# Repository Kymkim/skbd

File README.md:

# SKBD

!WORK IN PROGRESS

This is a keyboard project that I have been working on. This unlike your normal keyboard. This keyboard aims to solve my headaches with traditioal keyboards

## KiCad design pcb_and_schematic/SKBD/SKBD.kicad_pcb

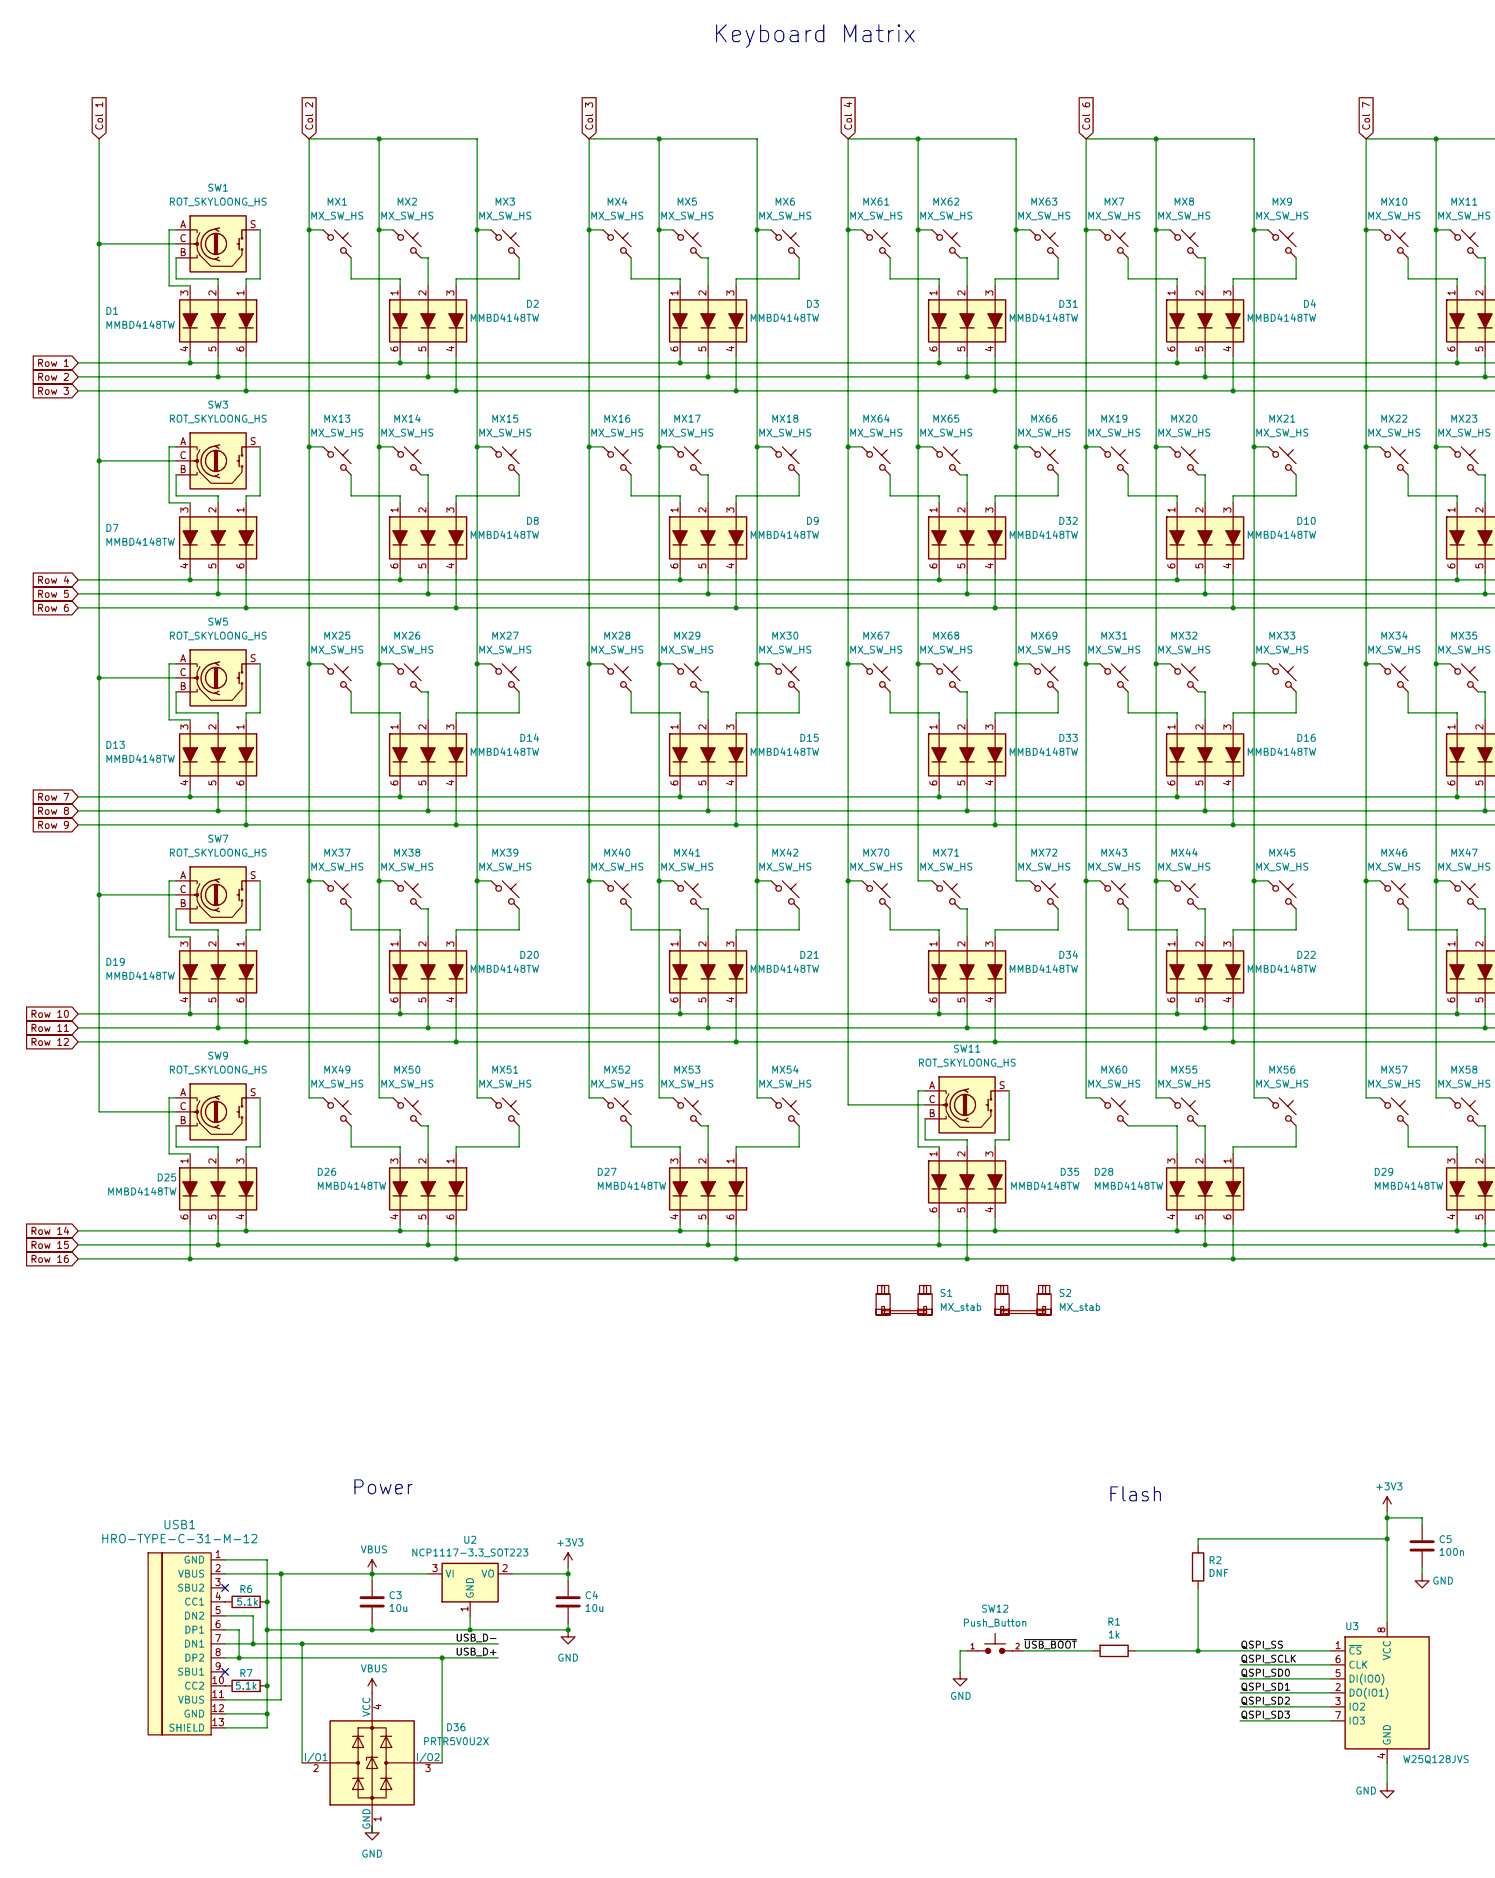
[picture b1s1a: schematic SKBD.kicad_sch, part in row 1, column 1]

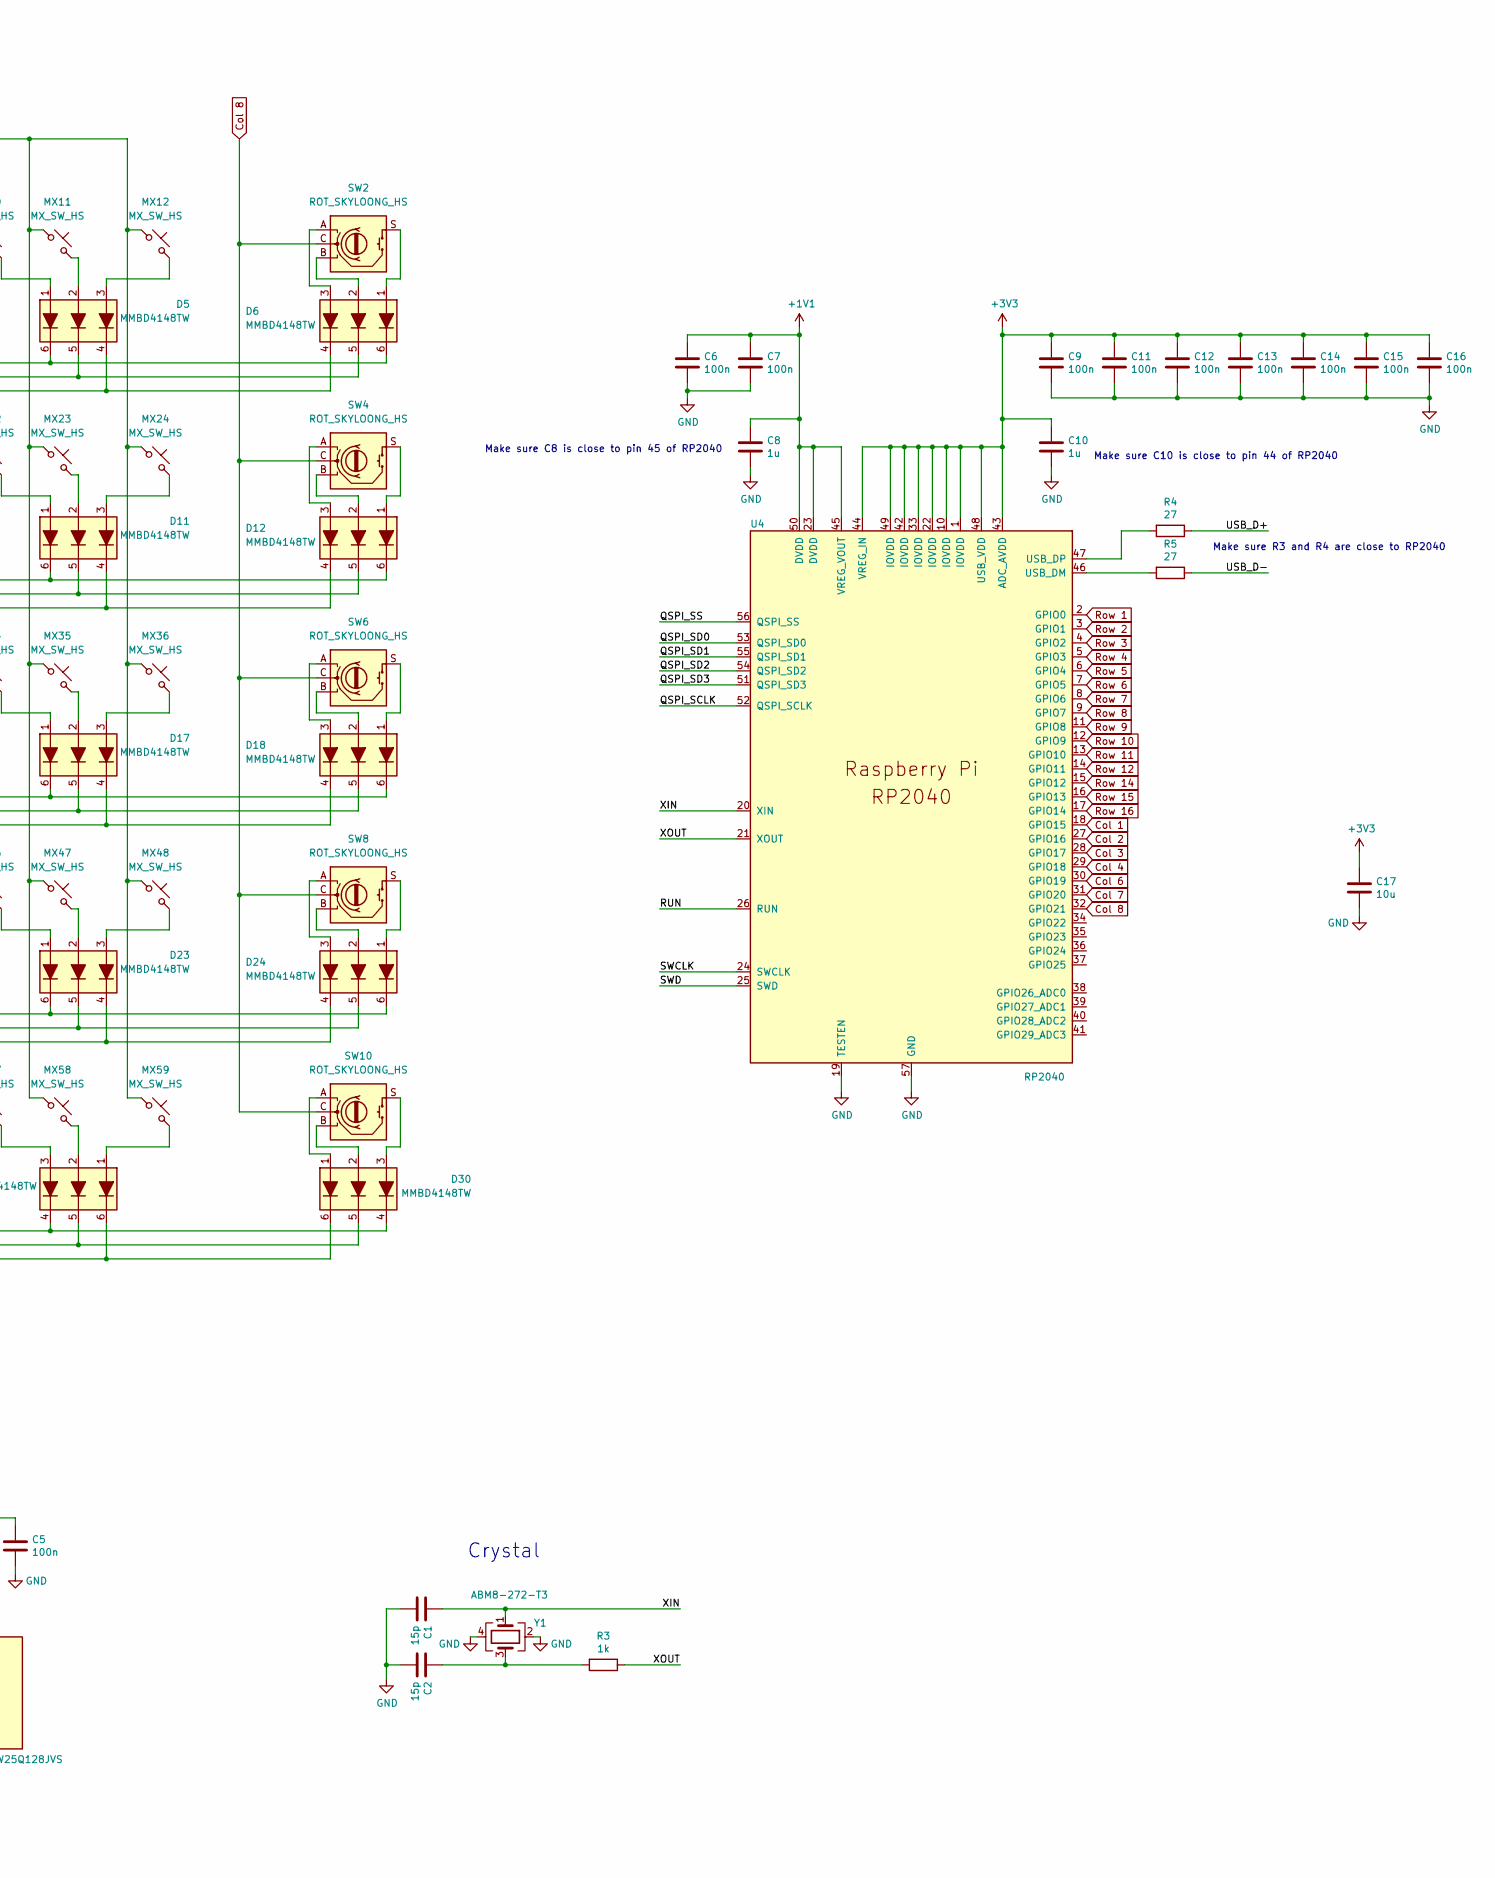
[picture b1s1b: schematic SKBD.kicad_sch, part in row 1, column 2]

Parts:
C1, C2: 15p; C_0402_1005Metric
C3, C4, C17: 10u; C_0402_1005Metric
C5, C6, C7, C9, C11, C12, C13, C14, C15, C16: 100n; C_0402_1005Metric
C8, C10: 1u; C_0402_1005Metric
D1, D2, D3, D4, D5, D6, D7, D8, D9, D10, D11, D12, D13, D14, D15, D16, D17, D18, D19, D20, D21, D22, D23, D24, D25, D26, D27, D28, D29, D30, D31, D32, D33, D34, D35: MMBD4148TW; SOT-363_SC-70-6
D36: PRTR5V0U2X; SOT-143
MX1, MX2, MX3, MX4, MX5, MX6, MX7, MX8, MX9, MX10, MX11, MX12, MX13, MX14, MX15, MX16, MX17, MX18, MX19, MX20, MX21, MX22, MX23, MX24, MX25, MX26, MX27, MX28, MX29, MX30, MX31, MX32, MX33, MX34, MX35, MX36, MX37, MX38, MX39, MX40, MX41, MX42, MX43, MX44, MX45, MX46, MX47, MX48, MX49, MX50, MX51, MX52, MX53, MX54, MX55, MX56, MX57, MX58, MX59, MX60, MX61, MX62, MX63, MX64, MX65, MX66, MX67, MX68, MX69, MX70, MX71, MX72: MX_SW_HS; SW_MX_HS_CPG151101S11_1u
R1, R3: 1k; R_0402_1005Metric
R2: DNF; R_0402_1005Metric
R4, R5: 27; R_0402_1005Metric
R6, R7: 5.1k; R_0402_1005Metric
S1, S2: MX_stab; STAB_MX_P_2u
SW1, SW2, SW3, SW4, SW5, SW6, SW7, SW8, SW9, SW10, SW11: ROT_SKYLOONG_HS; ROT_SKYLOONG_HS-Switch
SW12: Push_Button; SW_SPST_SKQG_WithStem
U2: NCP1117-3.3_SOT223; SOT-223-3_TabPin2
U3: W25Q128JVS; SOIC-8_5.23x5.23mm_P1.27mm
U4: RP2040; QFN-56-1EP_7x7mm_P0.4mm_EP3.2x3.2mm
USB1: HRO-TYPE-C-31-M-12; HRO-TYPE-C-31-M-12-Assembly
Y1: ABM8-272-T3; Crystal_SMD_3225-4Pin_3.2x2.5mm

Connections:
+1V1: C6.1, C7.1, C8.1, U4.23 (DVDD), U4.45 (VREG_VOUT), U4.50 (DVDD)
+3V3: C4.1, C5.1, C9.1, C10.1, C11.1, C12.1, C13.1, C14.1, C15.1, C16.1, C17.1, R2.1, U2.2 (VO), U3.8 (VCC), U4.1 (IOVDD), U4.10 (IOVDD), U4.22 (IOVDD), U4.33 (IOVDD), U4.42 (IOVDD), U4.43 (ADC_AVDD), U4.44 (VREG_IN), U4.48 (USB_VDD), U4.49 (IOVDD)
/QSPI_SCLK: U3.6 (CLK), U4.52 (QSPI_SCLK)
/QSPI_SD0: U3.5 (DI(IO0)), U4.53 (QSPI_SD0)
/QSPI_SD1: U3.2 (DO(IO1)), U4.55 (QSPI_SD1)
/QSPI_SD2: U3.3 (IO2), U4.54 (QSPI_SD2)
/QSPI_SD3: U3.7 (IO3), U4.51 (QSPI_SD3)
/QSPI_SS: R1.1, R2.2, U3.1 (~CS), U4.56 (QSPI_SS)
/RUN: U4.26 (RUN)
/SWCLK: U4.24 (SWCLK)
/SWD: U4.25 (SWD)
/USB_D+: D36.3 (I/O2), R4.1, USB1.6 (DP1), USB1.8 (DP2)
/USB_D-: D36.2 (I/O1), R5.1, USB1.5 (DN2), USB1.7 (DN1)
/XIN: C1.1, U4.20 (XIN), Y1.1
/XOUT: R3.1, U4.21 (XOUT)
/~USB_BOOT: R1.2, SW12.2
Col 1: SW1.C, SW3.C, SW5.C, SW7.C, SW9.C, U4.18 (GPIO15)
Col 2: MX1.1, MX2.1, MX3.1, MX13.1, MX14.1, MX15.1, MX25.1, MX26.1, MX27.1, MX37.1, MX38.1, MX39.1, MX49.1, MX50.1, MX51.1, U4.27 (GPIO16)
Col 3: MX4.1, MX5.1, MX6.1, MX16.1, MX17.1, MX18.1, MX28.1, MX29.1, MX30.1, MX40.1, MX41.1, MX42.1, MX52.1, MX53.1, MX54.1, U4.28 (GPIO17)
Col 4: MX61.1, MX62.1, MX63.1, MX64.1, MX65.1, MX66.1, MX67.1, MX68.1, MX69.1, MX70.1, MX71.1, MX72.1, SW11.C, U4.29 (GPIO18)
Col 6: MX7.1, MX8.1, MX9.1, MX19.1, MX20.1, MX21.1, MX31.1, MX32.1, MX33.1, MX43.1, MX44.1, MX45.1, MX55.1, MX56.1, MX60.1, U4.30 (GPIO19)
Col 7: MX10.1, MX11.1, MX12.1, MX22.1, MX23.1, MX24.1, MX34.1, MX35.1, MX36.1, MX46.1, MX47.1, MX48.1, MX57.1, MX58.1, MX59.1, U4.31 (GPIO20)
Col 8: SW2.C, SW4.C, SW6.C, SW8.C, SW10.C, U4.32 (GPIO21)
GND: C1.2, C2.2, C3.2, C4.2, C5.2, C6.2, C7.2, C8.2, C9.2, C10.2, C11.2, C12.2, C13.2, C14.2, C15.2, C16.2, C17.2, D36.1 (GND), R6.2, R7.2, SW12.1, U2.1 (GND), U3.4 (GND), U4.19 (TESTEN), U4.57 (GND), USB1.1 (GND), USB1.12 (GND), USB1.13 (SHIELD), Y1.2, Y1.4
unnamed: C2.1, R3.2, Y1.3
unnamed: D1.1 (A1), SW1.S
unnamed: D1.2 (A2), SW1.B
unnamed: D1.3 (A3), SW1.A
unnamed: D2.1 (A1), MX1.2
unnamed: D2.2 (A2), MX2.2
unnamed: D2.3 (A3), MX3.2
unnamed: D3.1 (A1), MX4.2
unnamed: D3.2 (A2), MX5.2
unnamed: D3.3 (A3), MX6.2
unnamed: D4.1 (A1), MX7.2
unnamed: D4.2 (A2), MX8.2
unnamed: D4.3 (A3), MX9.2
unnamed: D5.1 (A1), MX10.2
unnamed: D5.2 (A2), MX11.2
unnamed: D5.3 (A3), MX12.2
unnamed: D6.1 (A1), SW2.S
unnamed: D6.2 (A2), SW2.B
unnamed: D6.3 (A3), SW2.A
unnamed: D7.1 (A1), SW3.S
unnamed: D7.2 (A2), SW3.B
unnamed: D7.3 (A3), SW3.A
unnamed: D8.1 (A1), MX13.2
unnamed: D8.2 (A2), MX14.2
unnamed: D8.3 (A3), MX15.2
unnamed: D9.1 (A1), MX16.2
unnamed: D9.2 (A2), MX17.2
unnamed: D9.3 (A3), MX18.2
unnamed: D10.1 (A1), MX19.2
unnamed: D10.2 (A2), MX20.2
unnamed: D10.3 (A3), MX21.2
unnamed: D11.1 (A1), MX22.2
unnamed: D11.2 (A2), MX23.2
unnamed: D11.3 (A3), MX24.2
unnamed: D12.1 (A1), SW4.S
unnamed: D12.2 (A2), SW4.B
unnamed: D12.3 (A3), SW4.A
unnamed: D13.1 (A1), SW5.S
unnamed: D13.2 (A2), SW5.B
unnamed: D13.3 (A3), SW5.A
unnamed: D14.1 (A1), MX25.2
unnamed: D14.2 (A2), MX26.2
unnamed: D14.3 (A3), MX27.2
unnamed: D15.1 (A1), MX28.2
unnamed: D15.2 (A2), MX29.2
unnamed: D15.3 (A3), MX30.2
unnamed: D16.1 (A1), MX31.2
unnamed: D16.2 (A2), MX32.2
unnamed: D16.3 (A3), MX33.2
unnamed: D17.1 (A1), MX34.2
unnamed: D17.2 (A2), MX35.2
unnamed: D17.3 (A3), MX36.2
unnamed: D18.1 (A1), SW6.S
unnamed: D18.2 (A2), SW6.B
unnamed: D18.3 (A3), SW6.A
unnamed: D19.1 (A1), SW7.S
unnamed: D19.2 (A2), SW7.B
unnamed: D19.3 (A3), SW7.A
unnamed: D20.1 (A1), MX37.2
unnamed: D20.2 (A2), MX38.2
unnamed: D20.3 (A3), MX39.2
unnamed: D21.1 (A1), MX40.2
unnamed: D21.2 (A2), MX41.2
unnamed: D21.3 (A3), MX42.2
unnamed: D22.1 (A1), MX43.2
unnamed: D22.2 (A2), MX44.2
unnamed: D22.3 (A3), MX45.2
unnamed: D23.1 (A1), MX46.2
unnamed: D23.2 (A2), MX47.2
unnamed: D23.3 (A3), MX48.2
unnamed: D24.1 (A1), SW8.S
unnamed: D24.2 (A2), SW8.B
unnamed: D24.3 (A3), SW8.A
unnamed: D25.1 (A1), SW9.A
unnamed: D25.2 (A2), SW9.B
unnamed: D25.3 (A3), SW9.S
unnamed: D26.1 (A1), MX51.2
unnamed: D26.2 (A2), MX50.2
unnamed: D26.3 (A3), MX49.2
unnamed: D27.1 (A1), MX54.2
unnamed: D27.2 (A2), MX53.2
unnamed: D27.3 (A3), MX52.2
unnamed: D28.1 (A1), MX56.2
unnamed: D28.2 (A2), MX55.2
unnamed: D28.3 (A3), MX60.2
unnamed: D29.1 (A1), MX59.2
unnamed: D29.2 (A2), MX58.2
unnamed: D29.3 (A3), MX57.2
unnamed: D30.1 (A1), SW10.A
unnamed: D30.2 (A2), SW10.B
unnamed: D30.3 (A3), SW10.S
unnamed: D31.1 (A1), MX61.2
unnamed: D31.2 (A2), MX62.2
unnamed: D31.3 (A3), MX63.2
unnamed: D32.1 (A1), MX64.2
unnamed: D32.2 (A2), MX65.2
unnamed: D32.3 (A3), MX66.2
unnamed: D33.1 (A1), MX67.2
unnamed: D33.2 (A2), MX68.2
unnamed: D33.3 (A3), MX69.2
unnamed: D34.1 (A1), MX70.2
unnamed: D34.2 (A2), MX71.2
unnamed: D34.3 (A3), MX72.2
unnamed: D35.1 (A1), SW11.A
unnamed: D35.2 (A2), SW11.B
unnamed: D35.3 (A3), SW11.S
unnamed: R5.2, U4.46 (USB_DM)
unnamed: R4.2, U4.47 (USB_DP)
unnamed: R6.1, USB1.4 (CC1)
unnamed: R7.1, USB1.10 (CC2)
Row 1: D1.4 (K3), D2.6 (K1), D3.6 (K1), D4.6 (K1), D5.6 (K1), D6.6 (K1), D31.6 (K1), U4.2 (GPIO0)
Row 2: D1.5 (K2), D2.5 (K2), D3.5 (K2), D4.5 (K2), D5.5 (K2), D6.5 (K2), D31.5 (K2), U4.3 (GPIO1)
Row 3: D1.6 (K1), D2.4 (K3), D3.4 (K3), D4.4 (K3), D5.4 (K3), D6.4 (K3), D31.4 (K3), U4.4 (GPIO2)
Row 4: D7.4 (K3), D8.6 (K1), D9.6 (K1), D10.6 (K1), D11.6 (K1), D12.6 (K1), D32.6 (K1), U4.5 (GPIO3)
Row 5: D7.5 (K2), D8.5 (K2), D9.5 (K2), D10.5 (K2), D11.5 (K2), D12.5 (K2), D32.5 (K2), U4.6 (GPIO4)
Row 6: D7.6 (K1), D8.4 (K3), D9.4 (K3), D10.4 (K3), D11.4 (K3), D12.4 (K3), D32.4 (K3), U4.7 (GPIO5)
Row 7: D13.4 (K3), D14.6 (K1), D15.6 (K1), D16.6 (K1), D17.6 (K1), D18.6 (K1), D33.6 (K1), U4.8 (GPIO6)
Row 8: D13.5 (K2), D14.5 (K2), D15.5 (K2), D16.5 (K2), D17.5 (K2), D18.5 (K2), D33.5 (K2), U4.9 (GPIO7)
Row 9: D13.6 (K1), D14.4 (K3), D15.4 (K3), D16.4 (K3), D17.4 (K3), D18.4 (K3), D33.4 (K3), U4.11 (GPIO8)
Row 10: D19.4 (K3), D20.6 (K1), D21.6 (K1), D22.6 (K1), D23.6 (K1), D24.6 (K1), D34.6 (K1), U4.12 (GPIO9)
Row 11: D19.5 (K2), D20.5 (K2), D21.5 (K2), D22.5 (K2), D23.5 (K2), D24.5 (K2), D34.5 (K2), U4.13 (GPIO10)
Row 12: D19.6 (K1), D20.4 (K3), D21.4 (K3), D22.4 (K3), D23.4 (K3), D24.4 (K3), D34.4 (K3), U4.14 (GPIO11)
Row 14: D25.4 (K3), D26.4 (K3), D27.4 (K3), D28.4 (K3), D29.4 (K3), D30.4 (K3), D35.4 (K3), U4.15 (GPIO12)
Row 15: D25.5 (K2), D26.5 (K2), D27.5 (K2), D28.5 (K2), D29.5 (K2), D30.5 (K2), D35.6 (K1), U4.16 (GPIO13)
Row 16: D25.6 (K1), D26.6 (K1), D27.6 (K1), D28.6 (K1), D29.6 (K1), D30.6 (K1), D35.5 (K2), U4.17 (GPIO14)
VBUS: C3.1, D36.4 (VCC), U2.3 (VI), USB1.2 (VBUS), USB1.11 (VBUS)

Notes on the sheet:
Make sure C8 is close to pin 45 of RP2040
Power
Crystal
Make sure C10 is close to pin 44 of RP2040
Keyboard Matrix
Flash
Make sure R3 and R4 are close to RP2040

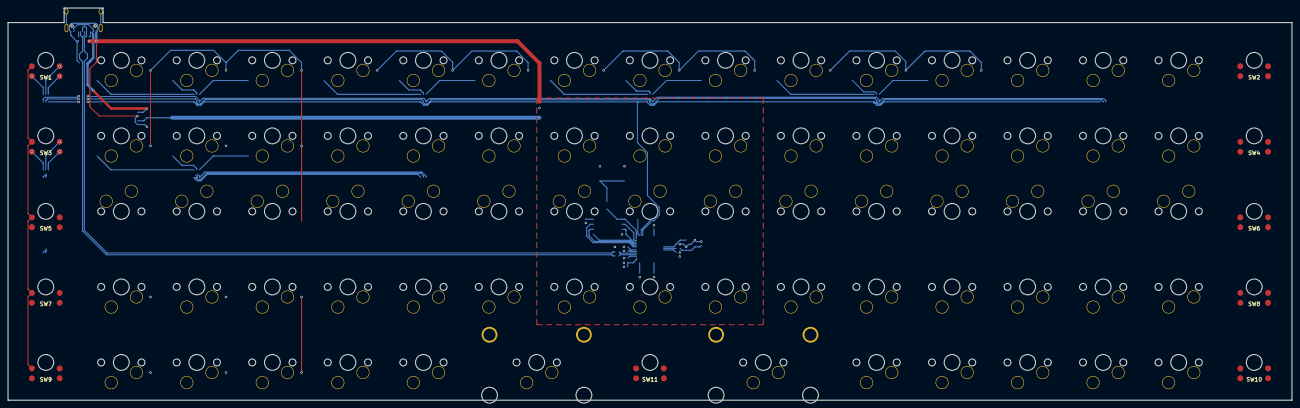
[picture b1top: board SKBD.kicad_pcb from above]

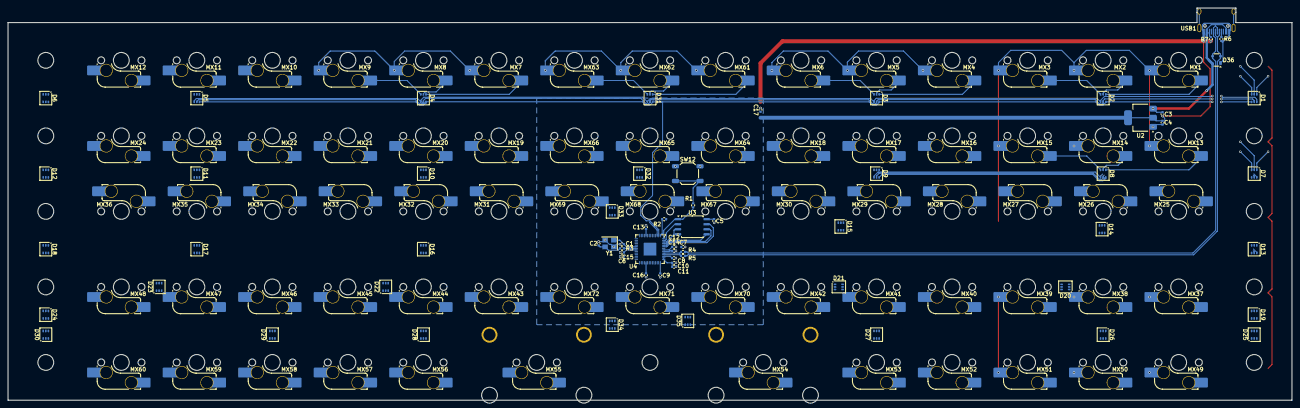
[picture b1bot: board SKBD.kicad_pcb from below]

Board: 2 copper layers, 323.9 x 98.9 mm, 151 parts (138 on the bottom side), 147 nets.

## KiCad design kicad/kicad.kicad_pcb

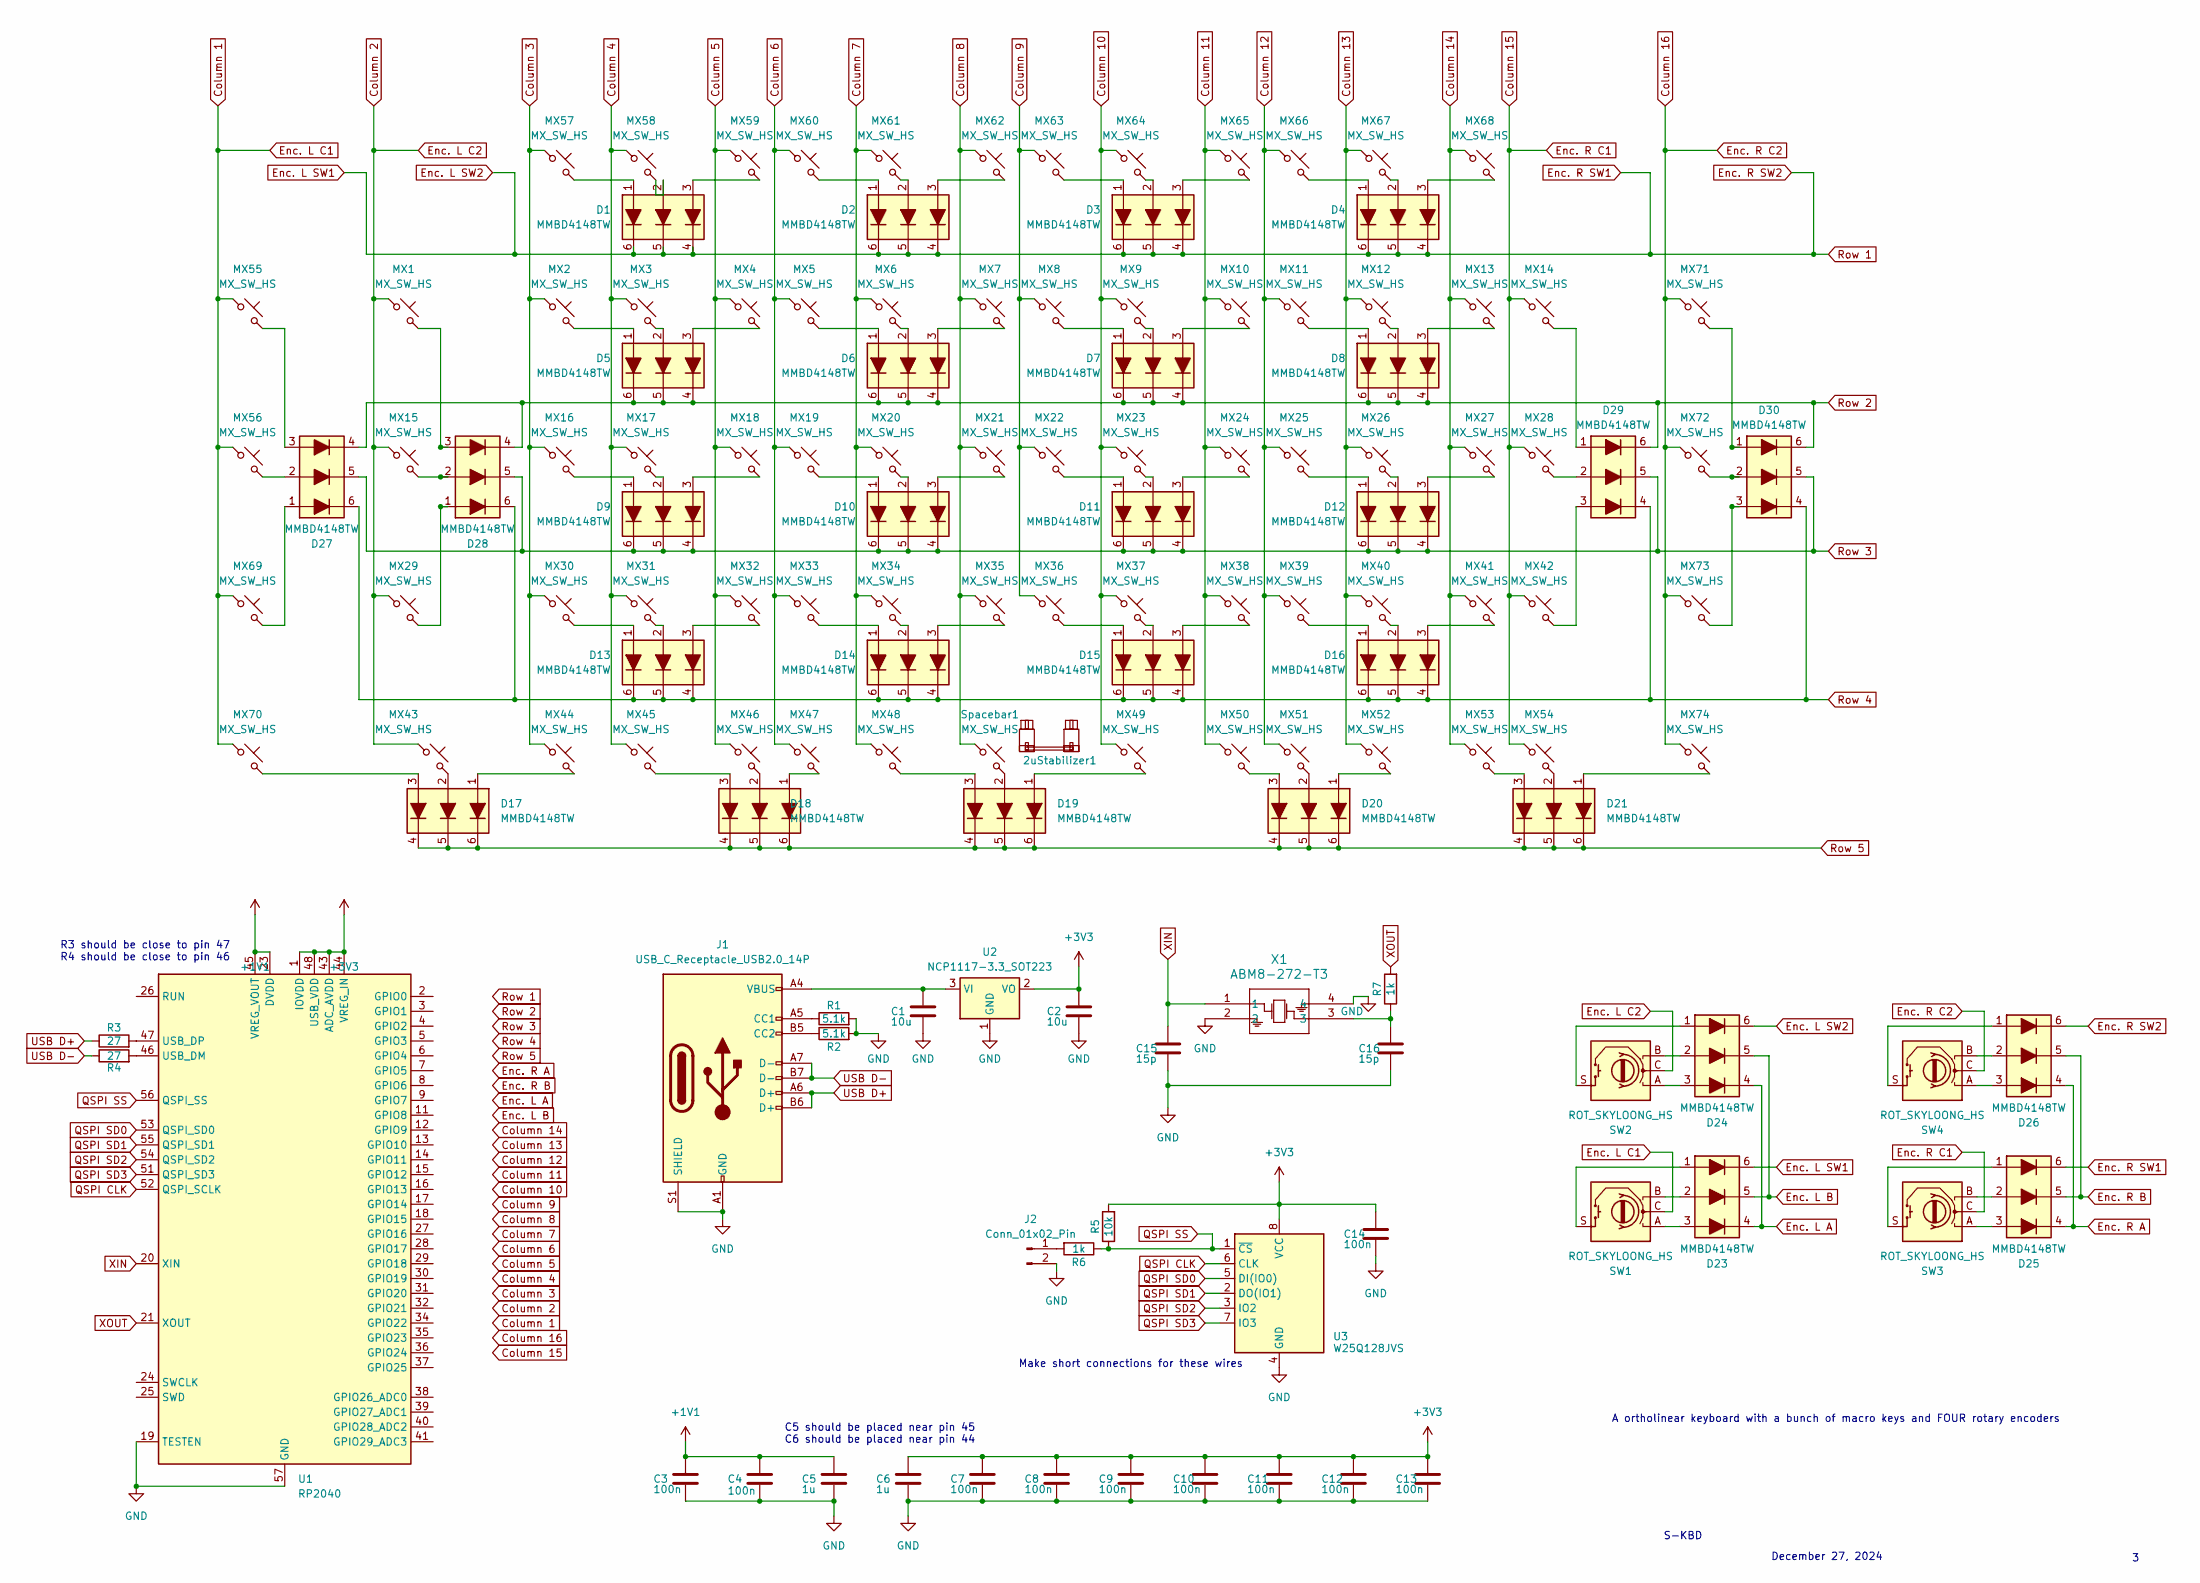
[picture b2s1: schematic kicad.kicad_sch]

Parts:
2uStabilizer1: MX_stab; STAB_MX_2u
C1, C2: 10u; C_01005_0402Metric
C3, C4, C7, C8, C9, C10, C11, C12, C13, C14: 100n; C_01005_0402Metric
C5, C6: 1u; C_01005_0402Metric
C15, C16: 15p; C_01005_0402Metric
D1, D2, D3, D4, D5, D6, D7, D8, D9, D10, D11, D12, D13, D14, D15, D16, D17, D18, D19, D20, D21, D23, D24, D25, D26, D27, D28, D29, D30: MMBD4148TW; SOT-363_SC-70-6
J1: USB_C_Receptacle_USB2.0_14P; USB_C_Receptacle_JAE_DX07S016JA1R1500
J2: Conn_01x02_Pin; PinHeader_1x02_P1.00mm_Horizontal
MX1, MX2, MX3, MX4, MX5, MX6, MX7, MX8, MX9, MX10, MX11, MX12, MX13, MX14, MX15, MX16, MX17, MX18, MX19, MX20, MX21, MX22, MX23, MX24, MX25, MX26, MX27, MX28, MX29, MX30, MX31, MX32, MX33, MX34, MX35, MX36, MX37, MX38, MX39, MX40, MX41, MX42, MX43, MX44, MX45, MX46, MX47, MX48, MX49, MX50, MX51, MX52, MX53, MX54, MX55, MX56, MX57, MX58, MX59, MX60, MX61, MX62, MX63, MX64, MX65, MX66, MX67, MX68, MX69, MX70, MX71, MX72, MX73, MX74: MX_SW_HS; SW_MX_HS_CPG151101S11_1u
R1, R2: 5.1k; R_01005_0402Metric
R3, R4: 27; R_01005_0402Metric
R5: 10k; R_01005_0402Metric
R6, R7: 1k; R_01005_0402Metric
SW1, SW2, SW3, SW4: ROT_SKYLOONG_HS; ROT_SKYLOONG_HS-Switch
Spacebar1: MX_SW_HS; SW_MX_HS_CPG151101S11_1u
U1: RP2040; QFN-56-1EP_7x7mm_P0.4mm_EP3.2x3.2mm
U2: NCP1117-3.3_SOT223; SOT-223-3_TabPin2
U3: W25Q128JVS; SOIC-8_5.23x5.23mm_P1.27mm
X1: ABM8-272-T3; ABM8-272-T3_ABR

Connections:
+1V1: C3.1, C4.1, C5.1, U1.23 (DVDD), U1.45 (VREG_VOUT), U1.50 (DVDD)
+3V3: C2.1, C6.1, C7.1, C8.1, C9.1, C10.1, C11.1, C12.1, C13.1, C14.1, R5.2, U1.1 (IOVDD), U1.10 (IOVDD), U1.22 (IOVDD), U1.33 (IOVDD), U1.42 (IOVDD), U1.43 (ADC_AVDD), U1.44 (VREG_IN), U1.48 (USB_VDD), U1.49 (IOVDD), U2.2 (VO), U3.8 (VCC)
Column 1: MX55.1, MX56.1, MX69.1, MX70.1, SW1.C
Column 2: MX1.1, MX15.1, MX29.1, MX43.1, SW2.C
Column 3: MX2.1, MX16.1, MX30.1, MX44.1, MX57.1
Column 4: MX3.1, MX17.1, MX31.1, MX45.1, MX58.1
Column 5: MX4.1, MX18.1, MX32.1, MX46.1, MX59.1
Column 6: MX5.1, MX19.1, MX33.1, MX47.1, MX60.1
Column 7: MX6.1, MX20.1, MX34.1, MX48.1, MX61.1
Column 8: MX7.1, MX21.1, MX35.1, MX62.1, Spacebar1.1
Column 9: MX8.1, MX22.1, MX36.1, MX63.1
Column 10: MX9.1, MX23.1, MX37.1, MX49.1, MX64.1
Column 11: MX10.1, MX24.1, MX38.1, MX50.1, MX65.1
Column 12: MX11.1, MX25.1, MX39.1, MX51.1, MX66.1
Column 13: MX12.1, MX26.1, MX40.1, MX52.1, MX67.1
Column 14: MX13.1, MX27.1, MX41.1, MX53.1, MX68.1
Column 15: MX14.1, MX28.1, MX42.1, MX54.1, SW3.C
Column 16: MX71.1, MX72.1, MX73.1, MX74.1, SW4.C
Enc. L A: D23.4 (K3), D24.4 (K3)
Enc. L B: D23.5 (K2), D24.5 (K2)
Enc. L SW1: D1.4 (K3), D1.5 (K2), D1.6 (K1), D2.4 (K3), D2.5 (K2), D2.6 (K1), D3.4 (K3), D3.5 (K2), D3.6 (K1), D4.4 (K3), D4.5 (K2), D4.6 (K1), D23.6 (K1), D24.6 (K1), D25.6 (K1), D26.6 (K1)
Enc. R A: D25.4 (K3), D26.4 (K3)
Enc. R B: D25.5 (K2), D26.5 (K2)
GND: C1.2, C2.2, C3.2, C4.2, C5.2, C6.2, C7.2, C8.2, C9.2, C10.2, C11.2, C12.2, C13.2, C14.2, C15.2, C16.2, J1.A1 (GND), J1.A12 (GND), J1.B1 (GND), J1.B12 (GND), J1.S1 (SHIELD), J2.2, R1.2, R2.2, U1.19 (TESTEN), U1.57 (GND), U2.1 (GND), U3.4 (GND), X1.2, X1.4
unnamed: C16.1, R7.1, X1.3
unnamed: D1.1 (A1), MX57.2
unnamed: D1.2 (A2), MX58.2
unnamed: D1.3 (A3), MX59.2
unnamed: D2.1 (A1), MX60.2
unnamed: D2.2 (A2), MX61.2
unnamed: D2.3 (A3), MX62.2
unnamed: D3.1 (A1), MX63.2
unnamed: D3.2 (A2), MX64.2
unnamed: D3.3 (A3), MX65.2
unnamed: D4.1 (A1), MX66.2
unnamed: D4.2 (A2), MX67.2
unnamed: D4.3 (A3), MX68.2
unnamed: D5.1 (A1), MX2.2
unnamed: D5.2 (A2), MX3.2
unnamed: D5.3 (A3), MX4.2
unnamed: D6.1 (A1), MX5.2
unnamed: D6.2 (A2), MX6.2
unnamed: D6.3 (A3), MX7.2
unnamed: D7.1 (A1), MX8.2
unnamed: D7.2 (A2), MX9.2
unnamed: D7.3 (A3), MX10.2
unnamed: D8.1 (A1), MX11.2
unnamed: D8.2 (A2), MX12.2
unnamed: D8.3 (A3), MX13.2
unnamed: D9.1 (A1), MX16.2
unnamed: D9.2 (A2), MX17.2
unnamed: D9.3 (A3), MX18.2
unnamed: D10.1 (A1), MX19.2
unnamed: D10.2 (A2), MX20.2
unnamed: D10.3 (A3), MX21.2
unnamed: D11.1 (A1), MX22.2
unnamed: D11.2 (A2), MX23.2
unnamed: D11.3 (A3), MX24.2
unnamed: D12.1 (A1), MX25.2
unnamed: D12.2 (A2), MX26.2
unnamed: D12.3 (A3), MX27.2
unnamed: D13.1 (A1), MX30.2
unnamed: D13.2 (A2), MX31.2
unnamed: D13.3 (A3), MX32.2
unnamed: D14.1 (A1), MX33.2
unnamed: D14.2 (A2), MX34.2
unnamed: D14.3 (A3), MX35.2
unnamed: D15.1 (A1), MX36.2
unnamed: D15.2 (A2), MX37.2
unnamed: D15.3 (A3), MX38.2
unnamed: D16.1 (A1), MX39.2
unnamed: D16.2 (A2), MX40.2
unnamed: D16.3 (A3), MX41.2
unnamed: D17.1 (A1), MX44.2
unnamed: D17.2 (A2), MX43.2
unnamed: D17.3 (A3), MX70.2
unnamed: D18.1 (A1), MX47.2
unnamed: D18.2 (A2), MX46.2
unnamed: D18.3 (A3), MX45.2
unnamed: D19.1 (A1), MX49.2
unnamed: D19.2 (A2), Spacebar1.2
unnamed: D19.3 (A3), MX48.2
unnamed: D20.1 (A1), MX52.2
unnamed: D20.2 (A2), MX51.2
unnamed: D20.3 (A3), MX50.2
unnamed: D21.1 (A1), MX74.2
unnamed: D21.2 (A2), MX54.2
unnamed: D21.3 (A3), MX53.2
unnamed: D23.1 (A1), SW1.S
unnamed: D23.2 (A2), SW1.B
unnamed: D23.3 (A3), SW1.A
unnamed: D24.1 (A1), SW2.S
unnamed: D24.2 (A2), SW2.B
unnamed: D24.3 (A3), SW2.A
unnamed: D25.1 (A1), SW3.S
unnamed: D25.2 (A2), SW3.B
unnamed: D25.3 (A3), SW3.A
unnamed: D26.1 (A1), SW4.S
unnamed: D26.2 (A2), SW4.B
unnamed: D26.3 (A3), SW4.A
unnamed: D27.1 (A1), MX69.2
unnamed: D27.2 (A2), MX56.2
unnamed: D27.3 (A3), MX55.2
unnamed: D28.1 (A1), MX29.2
unnamed: D28.2 (A2), MX15.2
unnamed: D28.3 (A3), MX1.2
unnamed: D29.1 (A1), MX14.2
unnamed: D29.2 (A2), MX28.2
unnamed: D29.3 (A3), MX42.2
unnamed: D30.1 (A1), MX71.2
unnamed: D30.2 (A2), MX72.2
unnamed: D30.3 (A3), MX73.2
unnamed: J1.A5 (CC1), R1.1
unnamed: J1.B5 (CC2), R2.1
unnamed: J2.1, R6.2
unnamed: R4.2, U1.46 (USB_DM)
unnamed: R3.2, U1.47 (USB_DP)
unnamed: C1.1, J1.A4 (VBUS), J1.A9 (VBUS), J1.B4 (VBUS), J1.B9 (VBUS), U2.3 (VI)
QSPI CLK: U1.52 (QSPI_SCLK), U3.6 (CLK)
QSPI SD0: U1.53 (QSPI_SD0), U3.5 (DI(IO0))
QSPI SD1: U1.55 (QSPI_SD1), U3.2 (DO(IO1))
QSPI SD2: U1.54 (QSPI_SD2), U3.3 (IO2)
QSPI SD3: U1.51 (QSPI_SD3), U3.7 (IO3)
QSPI SS: R5.1, R6.1, U1.56 (QSPI_SS), U3.1 (~CS)
Row 2: D5.4 (K3), D5.5 (K2), D5.6 (K1), D6.4 (K3), D6.5 (K2), D6.6 (K1), D7.4 (K3), D7.5 (K2), D7.6 (K1), D8.4 (K3), D8.5 (K2), D8.6 (K1), D27.4 (K3), D28.4 (K3), D29.6 (K1), D30.6 (K1)
Row 3: D9.4 (K3), D9.5 (K2), D9.6 (K1), D10.4 (K3), D10.5 (K2), D10.6 (K1), D11.4 (K3), D11.5 (K2), D11.6 (K1), D12.4 (K3), D12.5 (K2), D12.6 (K1), D27.5 (K2), D28.5 (K2), D29.5 (K2), D30.5 (K2)
Row 4: D13.4 (K3), D13.5 (K2), D13.6 (K1), D14.4 (K3), D14.5 (K2), D14.6 (K1), D15.4 (K3), D15.5 (K2), D15.6 (K1), D16.4 (K3), D16.5 (K2), D16.6 (K1), D27.6 (K1), D28.6 (K1), D29.4 (K3), D30.4 (K3)
Row 5: D17.4 (K3), D17.5 (K2), D17.6 (K1), D18.4 (K3), D18.5 (K2), D18.6 (K1), D19.4 (K3), D19.5 (K2), D19.6 (K1), D20.4 (K3), D20.5 (K2), D20.6 (K1), D21.4 (K3), D21.5 (K2), D21.6 (K1)
USB D+: J1.A6 (D+), J1.B6 (D+), R3.1
USB D-: J1.A7 (D-), J1.B7 (D-), R4.1
XIN: C15.1, U1.20 (XIN), X1.1
XOUT: R7.2, U1.21 (XOUT)

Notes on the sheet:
S-KBD
December 27, 2024
Make short connections for these wires
C5 should be placed near pin 45 C6 should be placed near pin 44
A ortholinear keyboard with a bunch of macro keys and FOUR rotary encoders
R3 should be close to pin 47 R4 should be close to pin 46

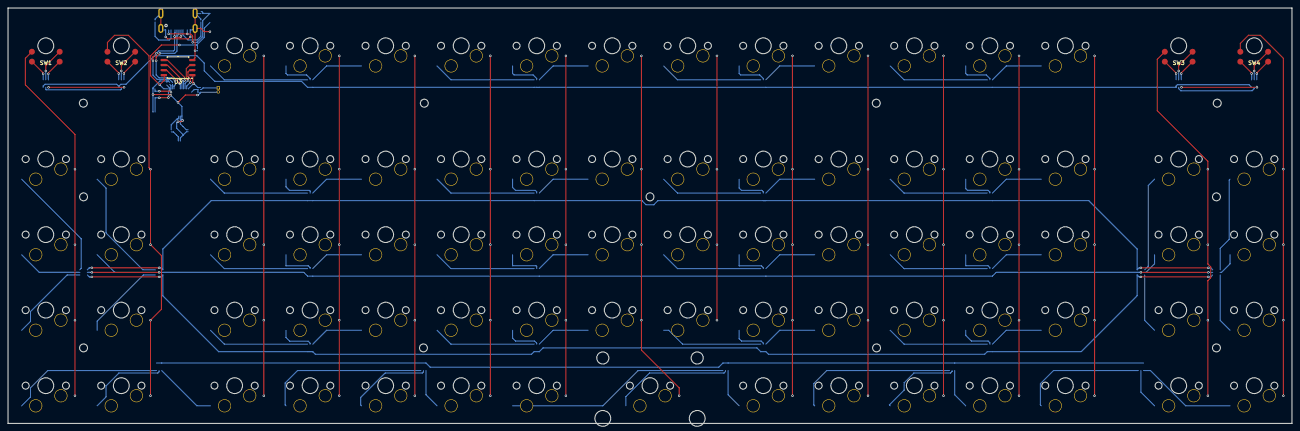
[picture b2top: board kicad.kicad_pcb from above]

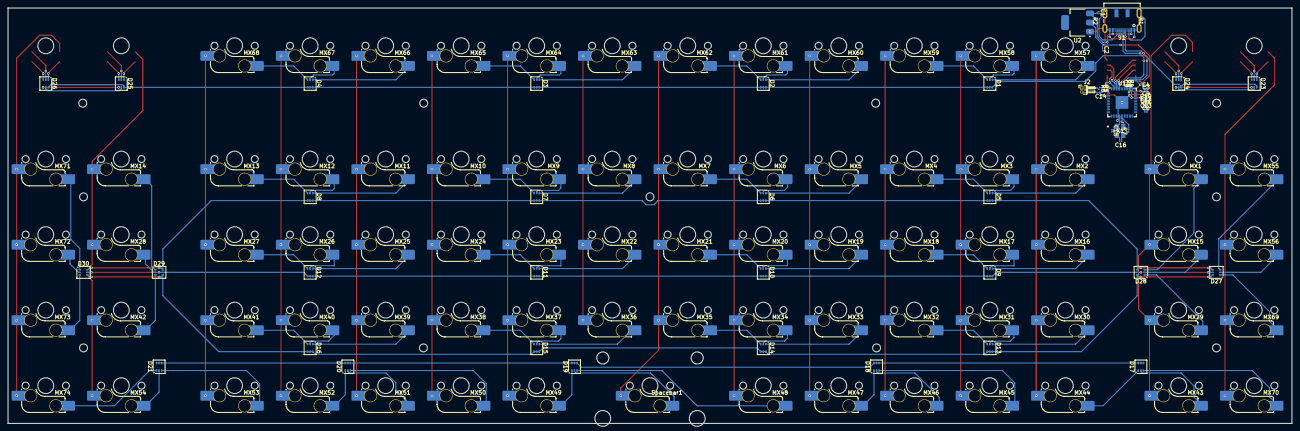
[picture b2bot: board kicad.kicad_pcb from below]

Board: 2 copper layers, 323.8 x 104.8 mm, 138 parts (133 on the bottom side), 132 nets.

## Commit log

2025-01-07 overhaul
2025-01-07 revision
2025-01-09 wiring
2025-01-10 wiring update
2025-01-14 wiring change
2025-01-18 rehaug
2025-01-18 rehaul
2025-01-19 Yet another overhaul
2025-01-19 modules and stuff
2025-01-21 revert to old desing
2025-01-29 files cleanup added edge cuts
